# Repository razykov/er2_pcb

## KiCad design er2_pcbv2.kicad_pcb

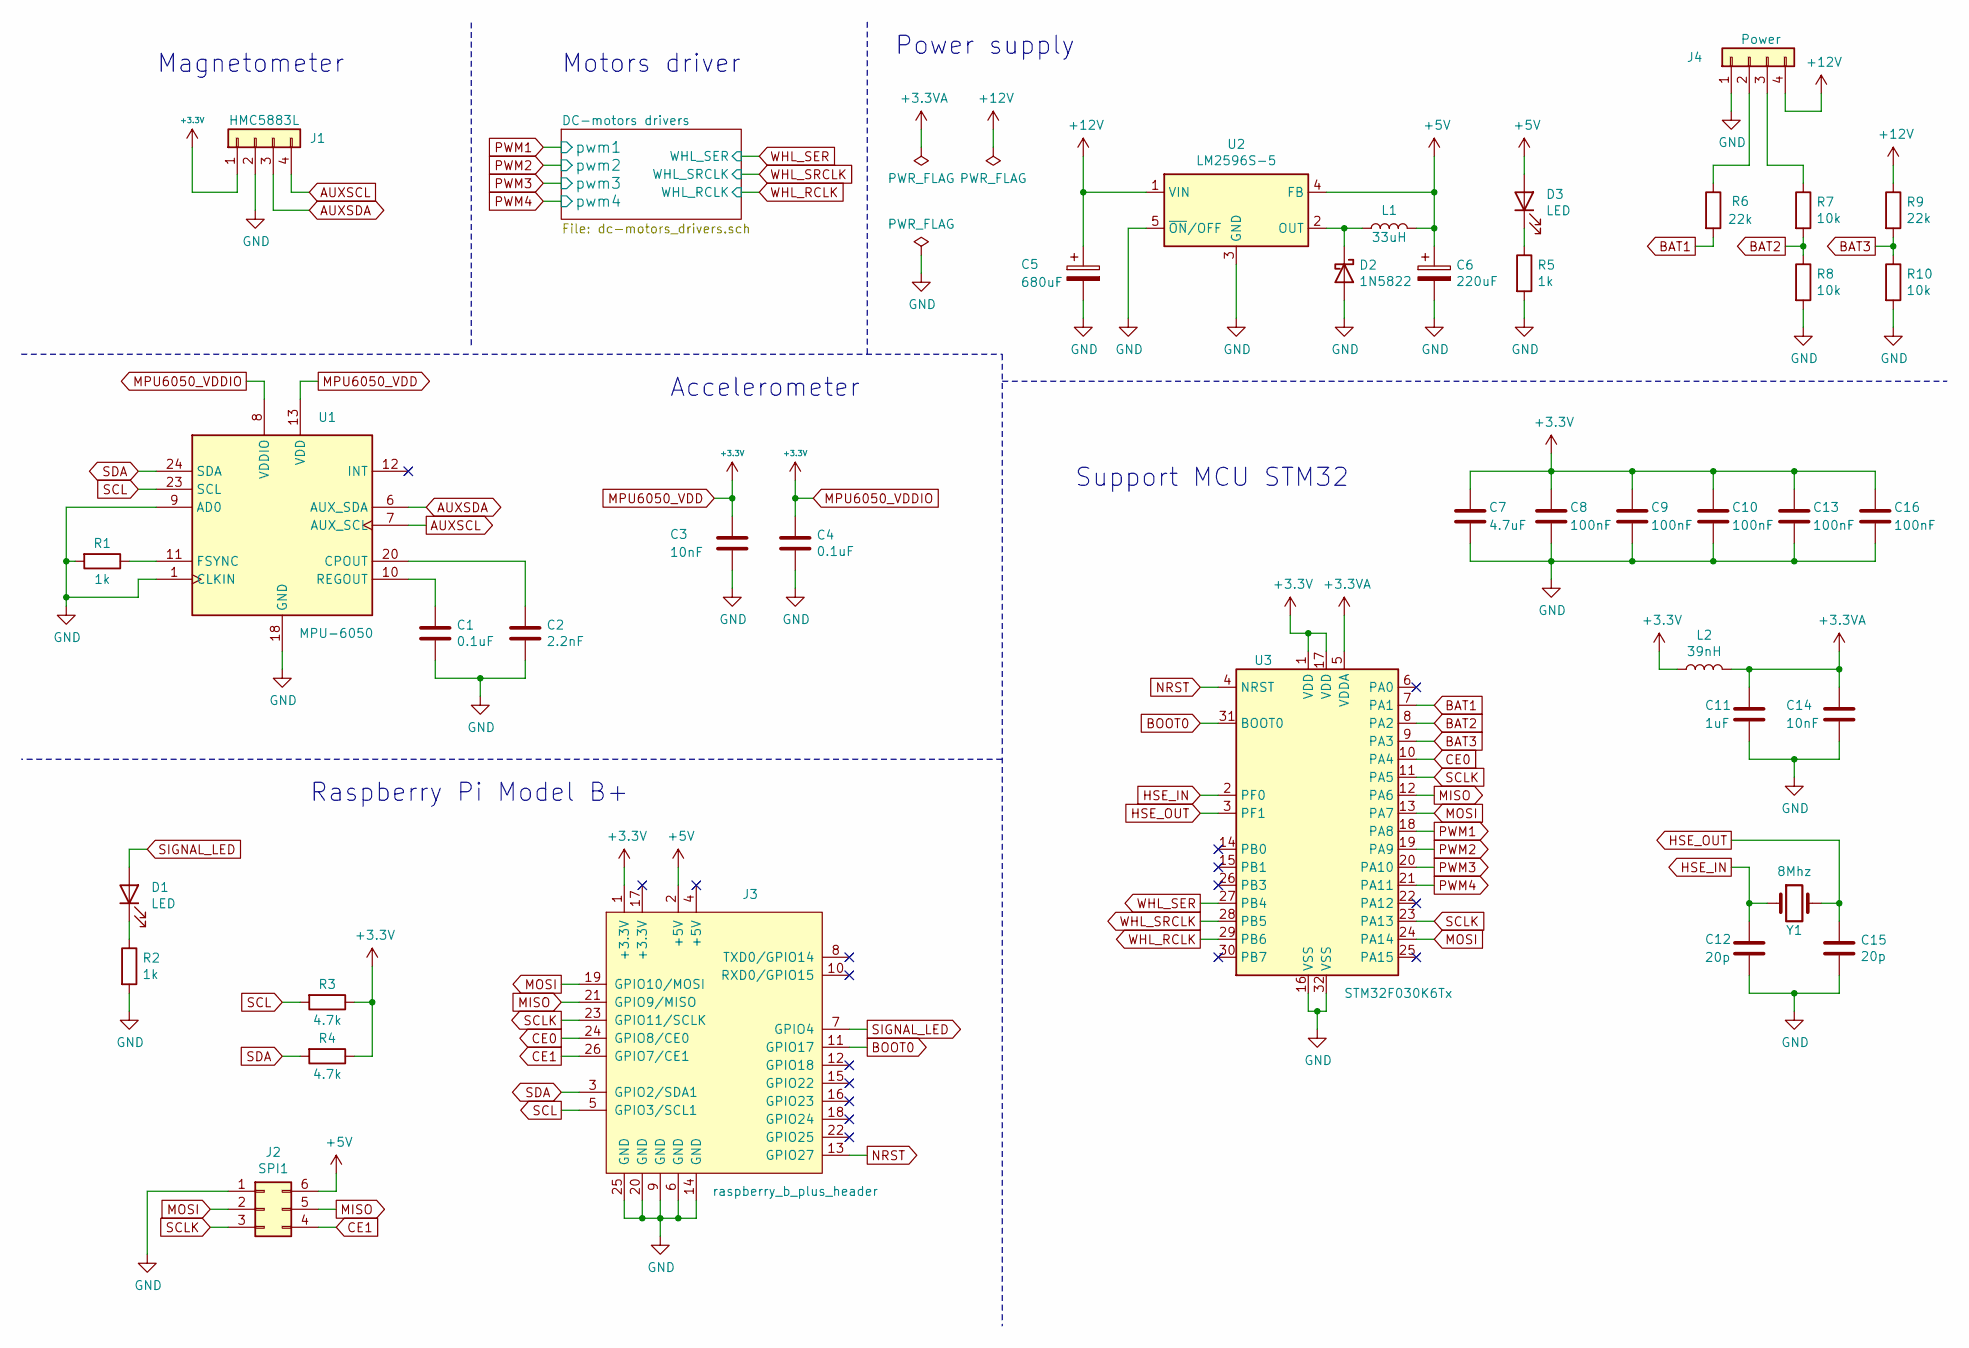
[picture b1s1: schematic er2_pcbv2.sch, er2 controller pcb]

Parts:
C1, C4: 0.1uF; C_0805_2012Metric_Pad1.18x1.45mm_HandSolder
C2: 2.2nF; C_0805_2012Metric_Pad1.18x1.45mm_HandSolder
C3, C14: 10nF; C_0805_2012Metric_Pad1.18x1.45mm_HandSolder
C5: 680uF; CP_Elec_10x10.5
C6: 220uF; CP_Elec_6.3x7.7
C7: 4.7uF; C_0805_2012Metric_Pad1.18x1.45mm_HandSolder
C8, C9, C10, C13, C16: 100nF; C_0805_2012Metric_Pad1.18x1.45mm_HandSolder
C11: 1uF; C_0805_2012Metric_Pad1.18x1.45mm_HandSolder
C12, C15: 20p; C_0805_2012Metric_Pad1.18x1.45mm_HandSolder
D1, D3: LED; LED_0805_2012Metric_Pad1.15x1.40mm_HandSolder
D2: 1N5822; D_SMA_Handsoldering
J1: HMC5883L; JST_GH_BM04B-GHS-TBT_1x04-1MP_P1.25mm_Vertical
J2: SPI1; JST_GH_BM05B-GHS-TBT_1x05-1MP_P1.25mm_Vertical
J3: raspberry_b_plus_header; PinHeader_2x13_P2.54mm_Vertical
J4: Power; JST_XH_B4B-XH-A_1x04_P2.50mm_Vertical
L1: 33uH; L_7.3x7.3_H3.5
L2: 39nH; L_0603_1608Metric_Pad1.05x0.95mm_HandSolder
R1, R2, R5: 1k; R_0805_2012Metric_Pad1.20x1.40mm_HandSolder
R3, R4: 4.7k; R_0805_2012Metric_Pad1.20x1.40mm_HandSolder
R6, R9: 22k; R_0805_2012Metric_Pad1.20x1.40mm_HandSolder
R7, R8, R10: 10k; R_0805_2012Metric_Pad1.20x1.40mm_HandSolder
U1: MPU-6050; InvenSense_QFN-24_4x4mm_P0.5mm
U2: LM2596S-5; TO-263-5_TabPin3
U3: STM32F030K6Tx; LQFP-32_7x7mm_P0.8mm
Y1: 8Mhz; Crystal_SMD_HC49-SD_HandSoldering

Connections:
+3.3VA: C11.1, C14.1, L2.2, U3.5 (VDDA)
+5V: C6.1, D3.2 (A), J2.6, J3.2 (+5V), L1.2, U2.4 (FB)
+12V: C5.1, J4.4, R9.1, U2.1 (VIN); also elsewhere on the board
AUXSCL: J1.4, U1.7 (AUX_SCL)
AUXSDA: J1.3, U1.6 (AUX_SDA)
BAT1: R6.2, U3.7 (PA1)
BAT2: R7.2, R8.1, U3.8 (PA2)
BAT3: R9.2, R10.1, U3.9 (PA3)
BOOT0: J3.11 (GPIO17), U3.31 (BOOT0)
CE0: J3.24 (GPIO8/CE0), U3.10 (PA4)
CE1: J2.4, J3.26 (GPIO7/CE1)
GND: C1.2, C2.2, C3.2, C4.2, C5.2, C6.2, C7.2, C8.2, C9.2, C10.2, C11.2, C12.2, C13.2, C14.2, C15.2, C16.2, D2.2 (A), J1.2, J2.1, J2.MP, J3.6 (GND), J3.9 (GND), J3.14 (GND), J3.20 (GND), J3.25 (GND), J4.1, R1.2, R2.2, R5.2, R8.2, R10.2, U1.1 (CLKIN), U1.9 (AD0), U1.18 (GND), U2.3 (GND), U2.5 (~ON~/OFF), U3.16 (VSS), U3.32 (VSS); also elsewhere on the board
HSE_IN: C12.1, U3.2 (PF0), Y1.1
HSE_OUT: C15.1, U3.3 (PF1), Y1.2
MISO: J2.5, J3.21 (GPIO9/MISO), U3.12 (PA6)
MOSI: J2.2, J3.19 (GPIO10/MOSI), U3.13 (PA7), U3.24 (PA14)
MPU6050_VDD: C3.1, C4.1, C7.1, C8.1, C9.1, C10.1, C13.1, C16.1, J1.1, J3.1 (+3.3V), L2.1, R3.1, R4.1, U1.8 (VDDIO), U1.13 (VDD), U3.1 (VDD), U3.17 (VDD); also elsewhere on the board
NRST: J3.13 (GPIO27), U3.4 (NRST)
unnamed: C1.1, U1.10 (REGOUT)
unnamed: C2.1, U1.20 (CPOUT)
unnamed: D1.1 (K), R2.1
unnamed: D2.1 (K), L1.1, U2.2 (OUT)
unnamed: D3.1 (K), R5.1
unnamed: J4.2, R6.1
unnamed: J4.3, R7.1
unnamed: R1.1, U1.11 (FSYNC)
PWM1: U3.18 (PA8); also elsewhere on the board
PWM2: U3.19 (PA9); also elsewhere on the board
PWM3: U3.20 (PA10); also elsewhere on the board
PWM4: U3.21 (PA11); also elsewhere on the board
SCL: J3.5 (GPIO3/SCL1), R3.2, U1.23 (SCL)
SCLK: J2.3, J3.23 (GPIO11/SCLK), U3.11 (PA5), U3.23 (PA13)
SDA: J3.3 (GPIO2/SDA1), R4.2, U1.24 (SDA)
SIGNAL_LED: D1.2 (A), J3.7 (GPIO4)
WHL_RCLK: U3.29 (PB6); also elsewhere on the board
WHL_SER: U3.27 (PB4); also elsewhere on the board
WHL_SRCLK: U3.28 (PB5); also elsewhere on the board

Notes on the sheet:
Power supply
Motors driver
Magnetometer
Accelerometer
Raspberry Pi Model B+
Support MCU STM32

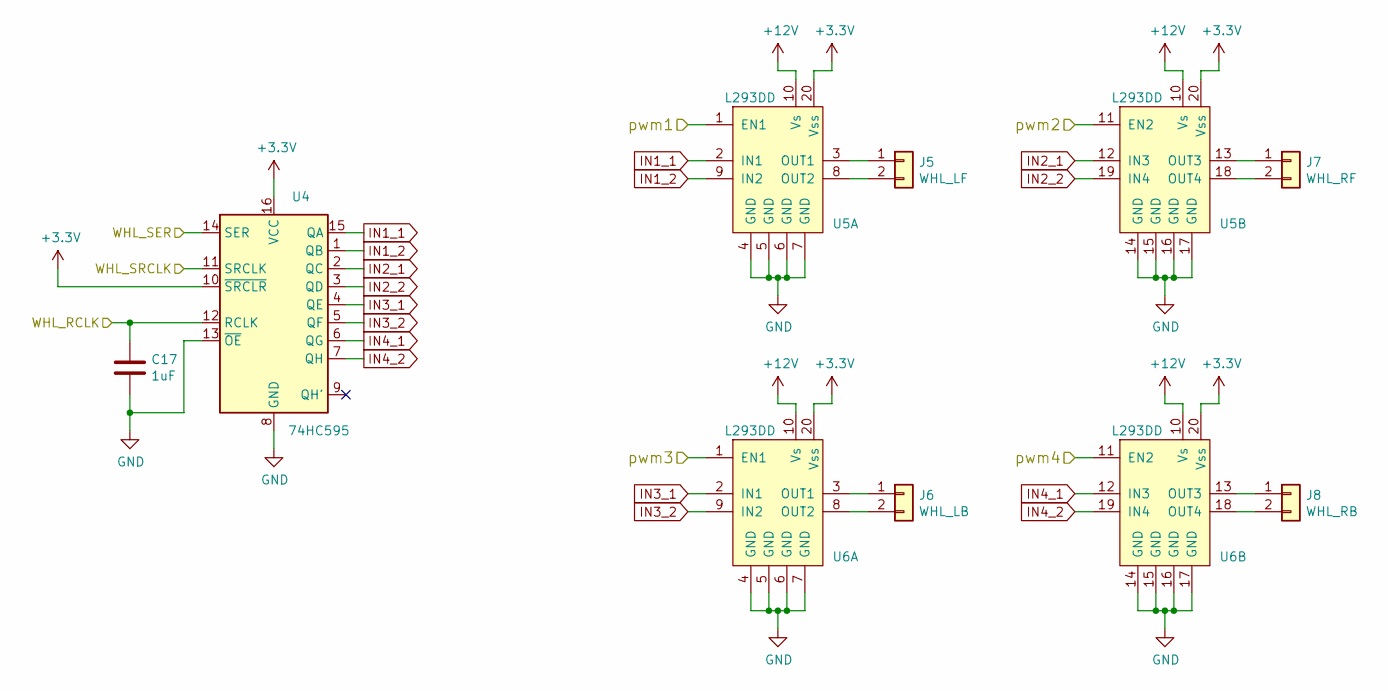
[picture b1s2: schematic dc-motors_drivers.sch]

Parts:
C17: 1uF; C_0805_2012Metric_Pad1.18x1.45mm_HandSolder
J5: WHL_LF; JST_PH_S2B-PH-K_1x02_P2.00mm_Horizontal
J6: WHL_LB; JST_PH_S2B-PH-K_1x02_P2.00mm_Horizontal
J7: WHL_RF; JST_PH_S2B-PH-K_1x02_P2.00mm_Horizontal
J8: WHL_RB; JST_PH_S2B-PH-K_1x02_P2.00mm_Horizontal
U4: 74HC595; SOP-16_4.4x10.4mm_P1.27mm
U5, U6: L293DD; SOP-20_7.5x12.8mm_P1.27mm

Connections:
+12V: U5.10 (Vs), U6.10 (Vs); also elsewhere on the board
GND: C17.2, U4.8 (GND), U4.13 (~OE), U5.4 (GND), U5.5 (GND), U5.6 (GND), U5.7 (GND), U5.14 (GND), U5.15 (GND), U5.16 (GND), U5.17 (GND), U6.4 (GND), U6.5 (GND), U6.6 (GND), U6.7 (GND), U6.14 (GND), U6.15 (GND), U6.16 (GND), U6.17 (GND); also elsewhere on the board
IN1_1: U4.15 (QA), U5.2 (IN1)
IN1_2: U4.1 (QB), U5.9 (IN2)
IN2_1: U4.2 (QC), U5.12 (IN3)
IN2_2: U4.3 (QD), U5.19 (IN4)
IN3_1: U4.4 (QE), U6.2 (IN1)
IN3_2: U4.5 (QF), U6.9 (IN2)
IN4_1: U4.6 (QG), U6.12 (IN3)
IN4_2: U4.7 (QH), U6.19 (IN4)
MPU6050_VDD: U4.10 (~SRCLR), U4.16 (VCC), U5.20 (Vss), U6.20 (Vss); also elsewhere on the board
unnamed: J5.1, U5.3 (OUT1)
unnamed: J5.2, U5.8 (OUT2)
unnamed: J6.1, U6.3 (OUT1)
unnamed: J6.2, U6.8 (OUT2)
unnamed: J7.1, U5.13 (OUT3)
unnamed: J7.2, U5.18 (OUT4)
unnamed: J8.1, U6.13 (OUT3)
unnamed: J8.2, U6.18 (OUT4)
PWM1: U5.1 (EN1); also elsewhere on the board
PWM2: U5.11 (EN2); also elsewhere on the board
PWM3: U6.1 (EN1); also elsewhere on the board
PWM4: U6.11 (EN2); also elsewhere on the board
WHL_RCLK: C17.1, U4.12 (RCLK); also elsewhere on the board
WHL_SER: U4.14 (SER); also elsewhere on the board
WHL_SRCLK: U4.11 (SRCLK); also elsewhere on the board

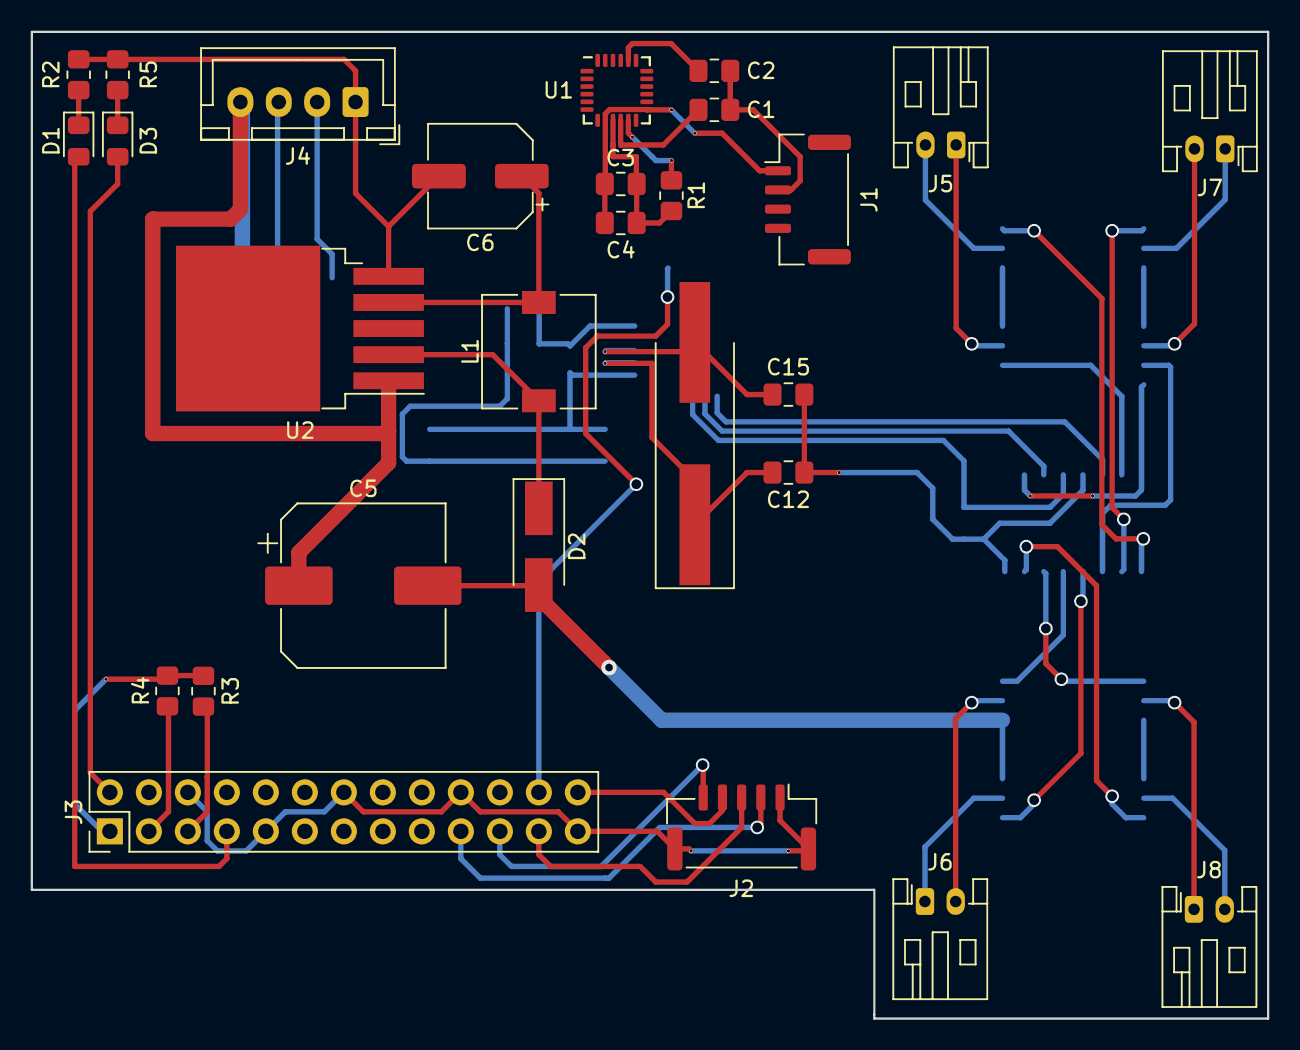
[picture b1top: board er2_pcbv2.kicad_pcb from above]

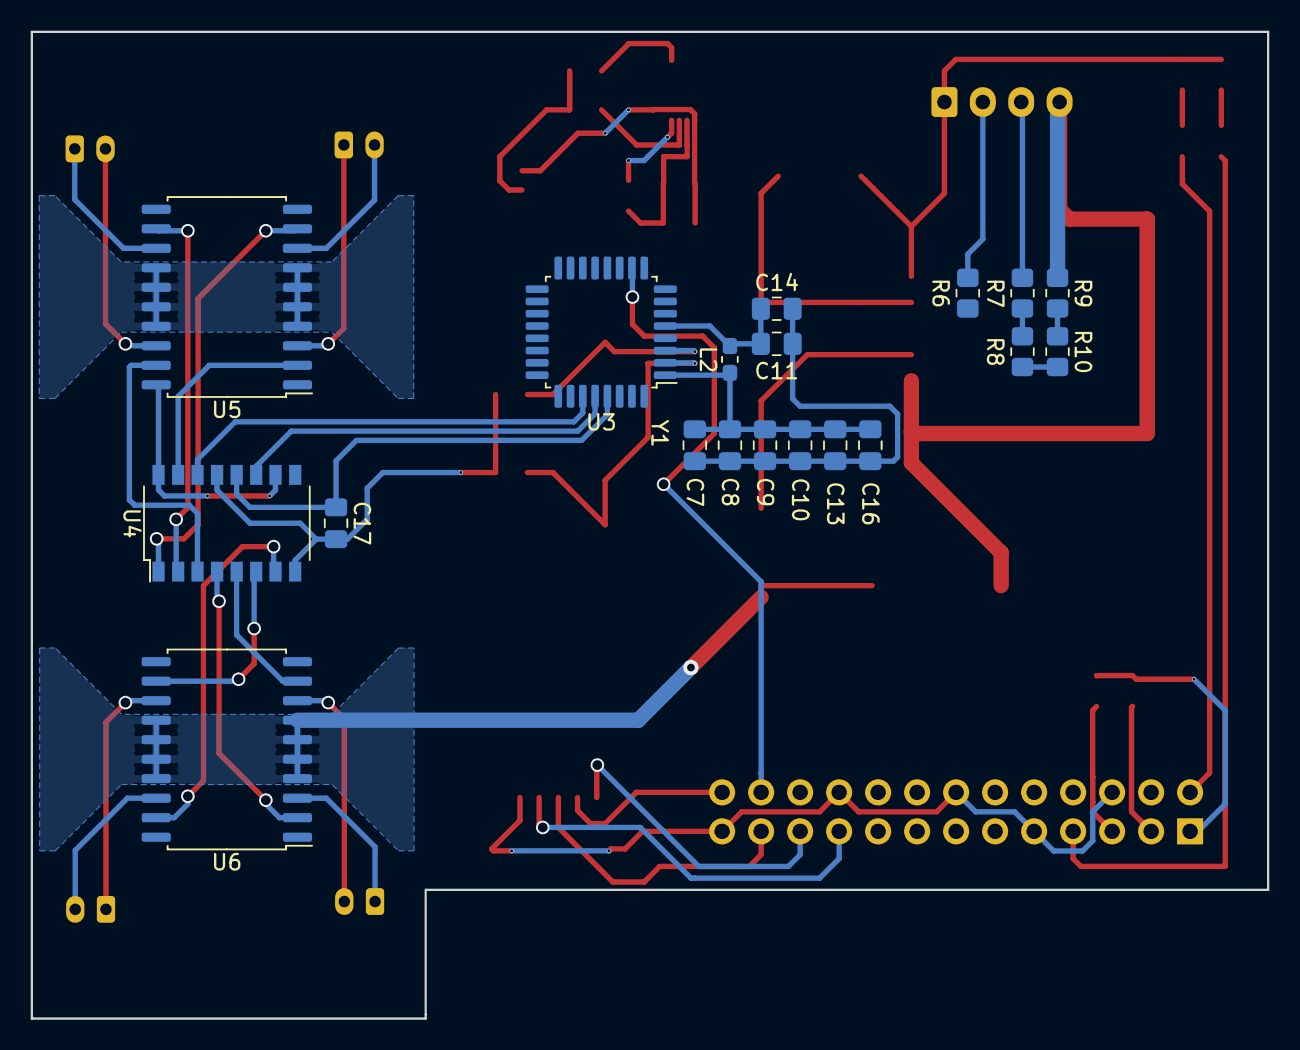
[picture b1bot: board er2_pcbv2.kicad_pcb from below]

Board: 2 copper layers, 80.5 x 64.3 mm, 47 parts (19 on the bottom side), 53 nets.

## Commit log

2015-04-29 add notes for pcbv2
2015-04-29 add pcbv2 scheme
2015-04-29 add gitignore
2015-04-29 add pcbv2 wire_net and footprints
2015-05-05 add indication to pcbv2
2015-05-24 pcb: 3.3v power supply added
2015-05-24 pcb: has been segmented
2015-05-24 pcb: accelerometer added
2015-06-12 pcb: RC-filters for PWM added
2015-08-13 components modules added
2015-08-13 slight changes before create pcb desigin
2015-08-13 pcb desigin file added
2015-08-13 pcb photomask drawing added. git status ! er2_pcbv2(rev1) FINISHED git status !
2015-08-13 all files moved to root
2016-03-09 kicad updated
2016-06-27 pcb: signal led resistor changed
2016-06-27 pcb: refresh footprints, accelerometer deleted
2016-06-27 pcb: RPi power supply deleted
2016-06-28 pcb: mma7455l replaced by mpu6050
2016-06-28 pcb: 74РС595 is conected SPI
2016-06-29 pcb: ADC PCF85911 batery control added
2016-06-29 listnet generate
2016-09-12 pcb layout added
2016-09-12 power supply 12V connector added
2016-09-12 pcb: silk placed exactly
2016-09-12 pcb: label and logo silk added
2016-09-15 pcb: SPI silk added
2016-09-16 pcb: silk small changes
2016-09-17 pcb: tracing optimization
2020-12-03 Scheme reborn
2020-12-03 packages of PCB components was assigned
2020-12-04 preliminary PCB components placement
